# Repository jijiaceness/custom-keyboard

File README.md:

# My Custom Keyboard: Overview

This is a fully custom 55-key split mechanical keyboard built from scratch, from the PCB to the 3D-printed case, developed with the support of Hack Club Program Keeb. 
I came into this project with almost no knowledge of how a keyboard works or the parts it consisted of, and over this two-month journey, I learned how to make all the components that make up a functional keyboard.

## Features
- Unique split keyboard layout
- Ergonomic ortholinear and column-staggered keys
- RJ45 socket connecting the two sides that supports hot-plugging
- 3D-printed top mount case with a base, plate, and top frame
- QMK firmware support with 3 custom layers

## Why I Built It

I've been wanting a split keyboard for a while after typing for hours on my laptop and experiencing hand pain and cramps. Mechanical keyboards have always appealed to me, and the Hack Club program Keeb was a great opportunity for me to build my own while learning the inner workings of a keyboard. I also liked the idea of how customizable my own keyboard would be as I could code what each key does instead of relying on the built-in funcitonality.

## What I Learned

Again, I came into this endeavor with no idea what a switch even was, so I most likely learned more from building this keyboard than in any of my year-long classes at school. 

I learned ...
- What a PCB actually does and its relation to a microcontroller
- How to make a PCB from scratch
- How to use Onshape and how to 3D-design with parametric modeling
- The different parts of a keyboard (switches, diodes, stabilizers, sockets, microcontroller, etc.)
- The software that makes your computer actually recognize and process keyboard input
- How to write the software and tailor it to my design
    - The relation between keymaps.c, keyboard.h, and info.json was particularly interesting; I didn't know that the matrix in info.json was based on the physical positioning of the switches

## Challenges

The biggest challenge was definitely getting used to the applications (KiCad and Onshape) and their workflow. Not understanding the right sequence and way to do things, even with the help of Keeb's guide, cost me many hours of redoing things and searching into the depths of the internet to fix.

  For KiCad, I didn't really finalize my layout on the schematic before moving onto the PCB editor and also put my left and right PCB on the same project, which went against KiCad's method of designing PCBs. I spent a lot of time moving the right PCB into a new project but still had to redo most of it.

  For Onshape, I had no idea how to properly constrain my sketches, and my first iterations were filled with haphazard lengths and angles. I probably redid my sketch 10 times while designing the case. I do feel proud now in how far I've come in CADing since the beginning, and my sketches are much cleaner now.

# Keyboard Overview

## Schematic
### Left schematic

### Right schematic

## PCB

### 3D view
|left view|right view|
| --- | --- |
|  |  |

## Case
### Left Case

<br>

### Right Case

<br>

# Bill of Materials (BOM)

|Item|Name                        |Quantity|Notes                                             |Cost (USD)|
|----|----------------------------|--------|--------------------------------------------------|----------|
|1   |Raspberry Pi Pico           |2       |SC0916                                            |$7.82     |
|2   |Left PCB from JLCPCB        |1       |                                                  |$13.8     |
|3   |Right PCB from JLCPCB       |1       |                                                  |$13.8     |
|4   |Cherry MX Switches          |55      |70 count, Orange key switch.                      |$16.8     |
|5   |1N4148 Diodes               |55      |100 count                                         |$3.91     |
|6   |M3xD4.6xL3.0 heatset inserts|52      |100 count                                         |$5.18     |
|7   |M3x5mm screws               |7       |50 count                                          |$2.56     |
|8   |M3x14mm screws              |6       |50 count                                          |$3.54     |
|9   |RJ45 Shield Network Jack    |2       |Comes in pack of 2, RJHSE-XM80                    |$3.82     |
|10  |Micro USB to USB-A Cable    |1       |1m                                                |$2.6      |
|11  |USB-A to USB-C adapter      |1       |                                                  |$3.45     |
|12  |Rj45 Connector              |1       |0.5m                                              |$4.37     |
|13  |DSA Blank Custom Keycaps    |62      |85 pcs (any keycaps bigger than 1u counts as 2 pcs|$32.94    |
|14  |                            |        |                                                  |          |
|    |TOTAL                       |        |                                                  |$114.59   |

# Credits

This project was possible due to the numerous open-source projects and resources, especially the [the keyther by MagoSaronno](https://github.com/MagoSaronno/keyther/tree/main) as well as many other detailed in the journal. Finally, thank you to Hack Club Keeb for providing the guides and opportunity for me to build a keyboard!

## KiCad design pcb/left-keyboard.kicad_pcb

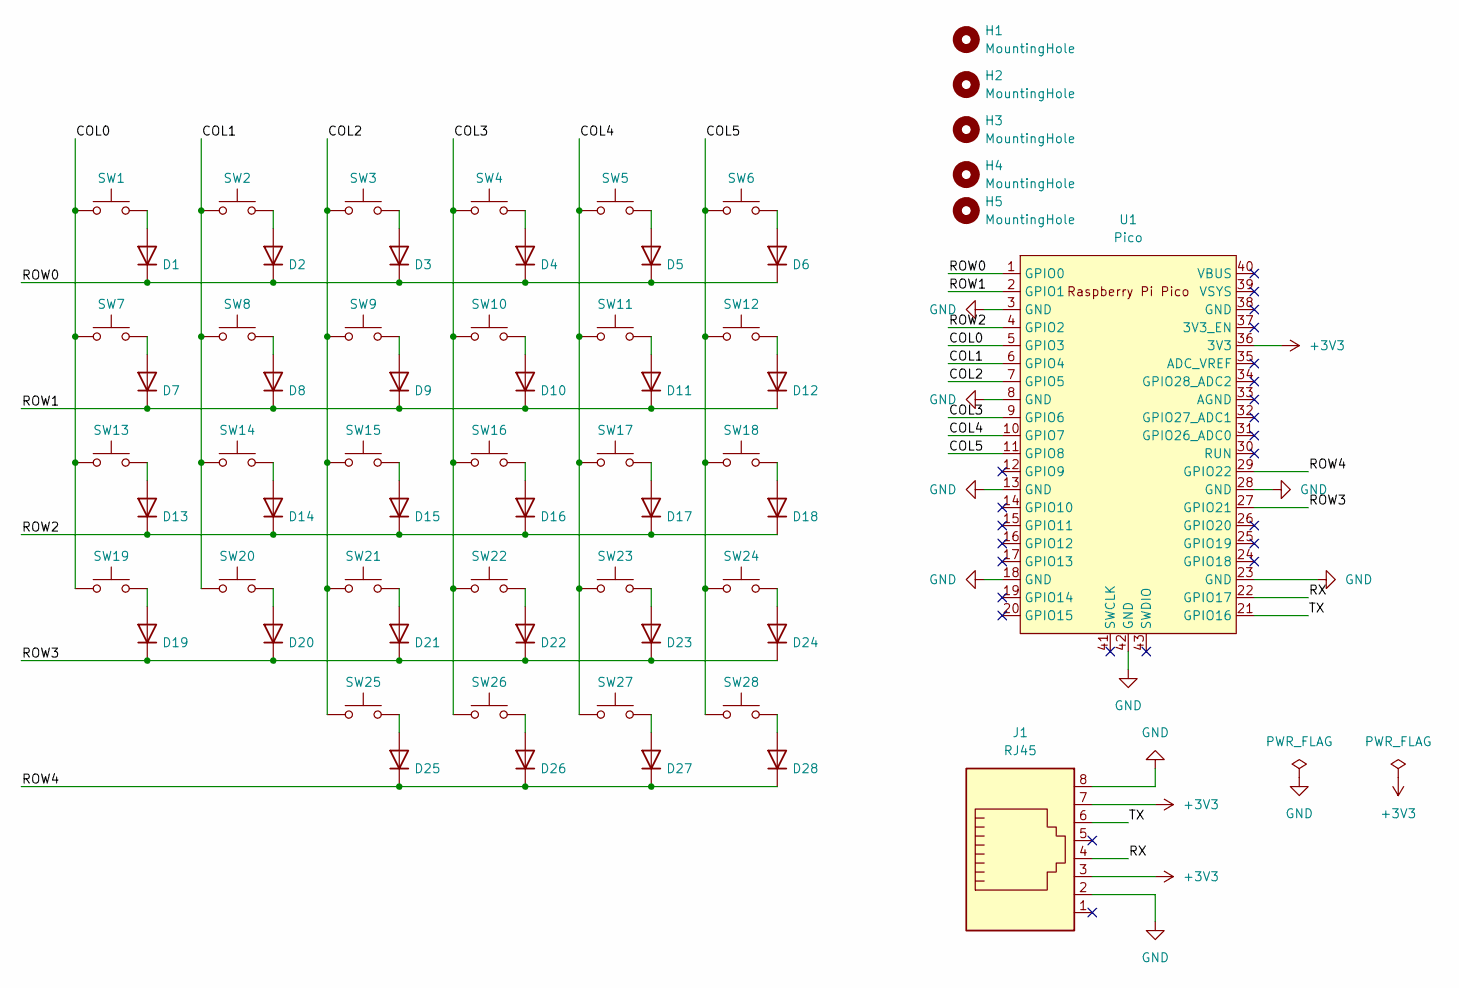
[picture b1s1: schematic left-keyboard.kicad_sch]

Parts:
D1, D2, D3, D4, D5, D6, D7, D8, D9, D10, D11, D12, D13, D14, D15, D16, D17, D18, D19, D20, D21, D22, D23, D24, D25, D26, D27, D28: 1N4148; D_DO-35_SOD27_P7.62mm_Horizontal
H1, H2, H3, H4, H5: MountingHole; MountingHole_3.2mm_M3
J1: RJ45; RJ45_Amphenol_RJHSE5380
SW1, SW2, SW3, SW4, SW5, SW6, SW8, SW9, SW10, SW11, SW12, SW14, SW15, SW16, SW17, SW18, SW20, SW21, SW22, SW23, SW24, SW25, SW26, SW27, SW28: SW_Push; SW_MX_1u
SW7: SW_Push; SW_MX_1.25u
SW13: SW_Push; SW_MX_1.5u
SW19: SW_Push; SW_MX_1.75u
U1: Pico; RPi_Pico_SMD_TH

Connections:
+3V3: J1.3, J1.7, U1.36 (3V3)
/COL0: SW1.1, SW7.1, SW13.1, SW19.1, U1.5 (GPIO3)
/COL1: SW2.1, SW8.1, SW14.1, SW20.1, U1.6 (GPIO4)
/COL2: SW3.1, SW9.1, SW15.1, SW21.1, SW25.1, U1.7 (GPIO5)
/COL3: SW4.1, SW10.1, SW16.1, SW22.1, SW26.1, U1.9 (GPIO6)
/COL4: SW5.1, SW11.1, SW17.1, SW23.1, SW27.1, U1.10 (GPIO7)
/COL5: SW6.1, SW12.1, SW18.1, SW24.1, SW28.1, U1.11 (GPIO8)
/ROW0: D1.1 (K), D2.1 (K), D3.1 (K), D4.1 (K), D5.1 (K), D6.1 (K), U1.1 (GPIO0)
/ROW1: D7.1 (K), D8.1 (K), D9.1 (K), D10.1 (K), D11.1 (K), D12.1 (K), U1.2 (GPIO1)
/ROW2: D13.1 (K), D14.1 (K), D15.1 (K), D16.1 (K), D17.1 (K), D18.1 (K), U1.4 (GPIO2)
/ROW3: D19.1 (K), D20.1 (K), D21.1 (K), D22.1 (K), D23.1 (K), D24.1 (K), U1.27 (GPIO21)
/ROW4: D25.1 (K), D26.1 (K), D27.1 (K), D28.1 (K), U1.29 (GPIO22)
/RX: J1.4, U1.22 (GPIO17)
/TX: J1.6, U1.21 (GPIO16)
GND: J1.2, J1.8, U1.3 (GND), U1.8 (GND), U1.13 (GND), U1.18 (GND), U1.23 (GND), U1.28 (GND), U1.42 (GND)
unnamed: D1.2 (A), SW1.2
unnamed: D2.2 (A), SW2.2
unnamed: D3.2 (A), SW3.2
unnamed: D4.2 (A), SW4.2
unnamed: D5.2 (A), SW5.2
unnamed: D6.2 (A), SW6.2
unnamed: D7.2 (A), SW7.2
unnamed: D8.2 (A), SW8.2
unnamed: D9.2 (A), SW9.2
unnamed: D10.2 (A), SW10.2
unnamed: D11.2 (A), SW11.2
unnamed: D12.2 (A), SW12.2
unnamed: D13.2 (A), SW13.2
unnamed: D14.2 (A), SW14.2
unnamed: D15.2 (A), SW15.2
unnamed: D16.2 (A), SW16.2
unnamed: D17.2 (A), SW17.2
unnamed: D18.2 (A), SW18.2
unnamed: D19.2 (A), SW19.2
unnamed: D20.2 (A), SW20.2
unnamed: D21.2 (A), SW21.2
unnamed: D22.2 (A), SW22.2
unnamed: D23.2 (A), SW23.2
unnamed: D24.2 (A), SW24.2
unnamed: D25.2 (A), SW25.2
unnamed: D26.2 (A), SW26.2
unnamed: D27.2 (A), SW27.2
unnamed: D28.2 (A), SW28.2

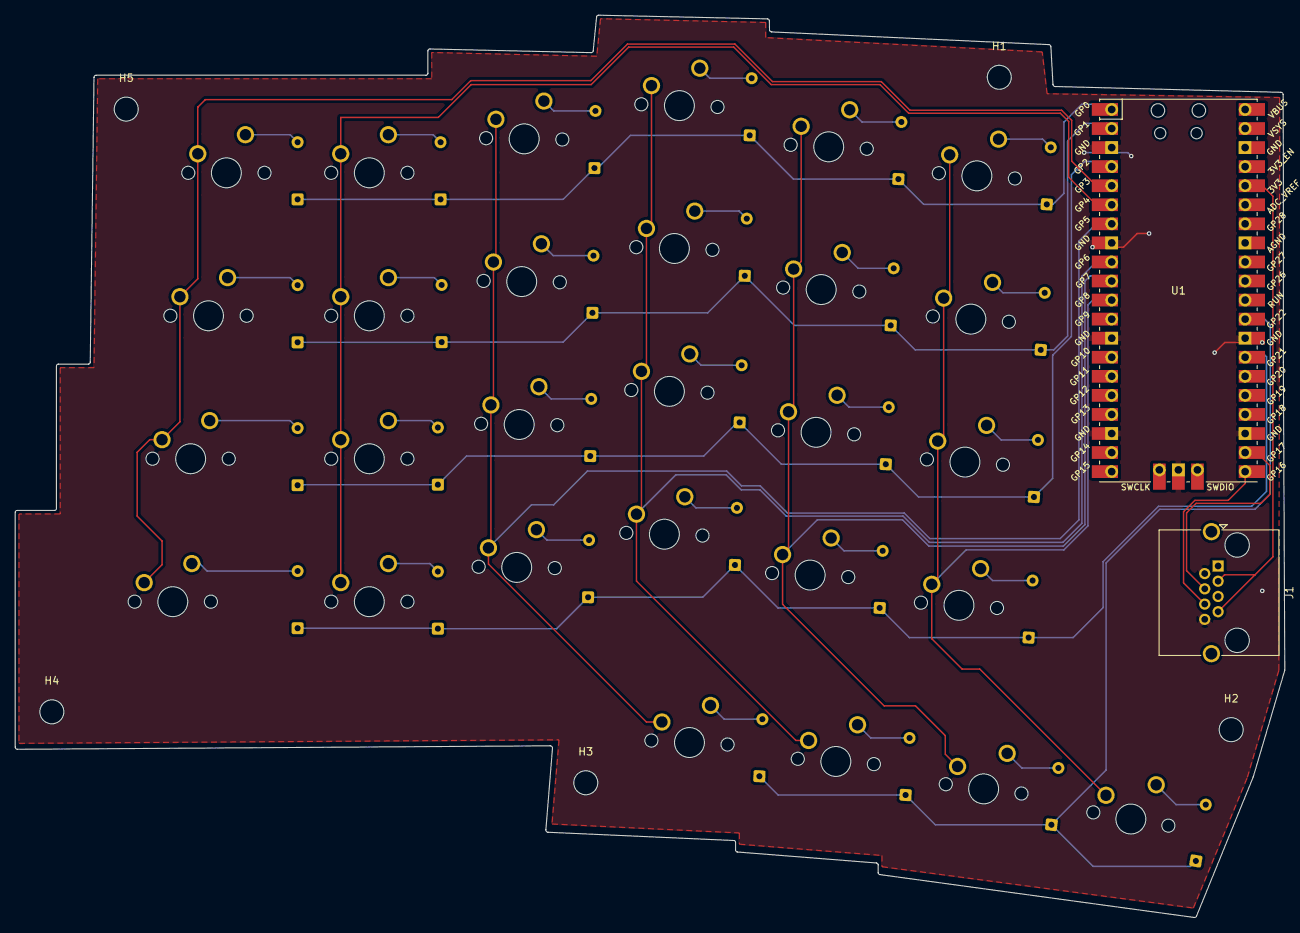
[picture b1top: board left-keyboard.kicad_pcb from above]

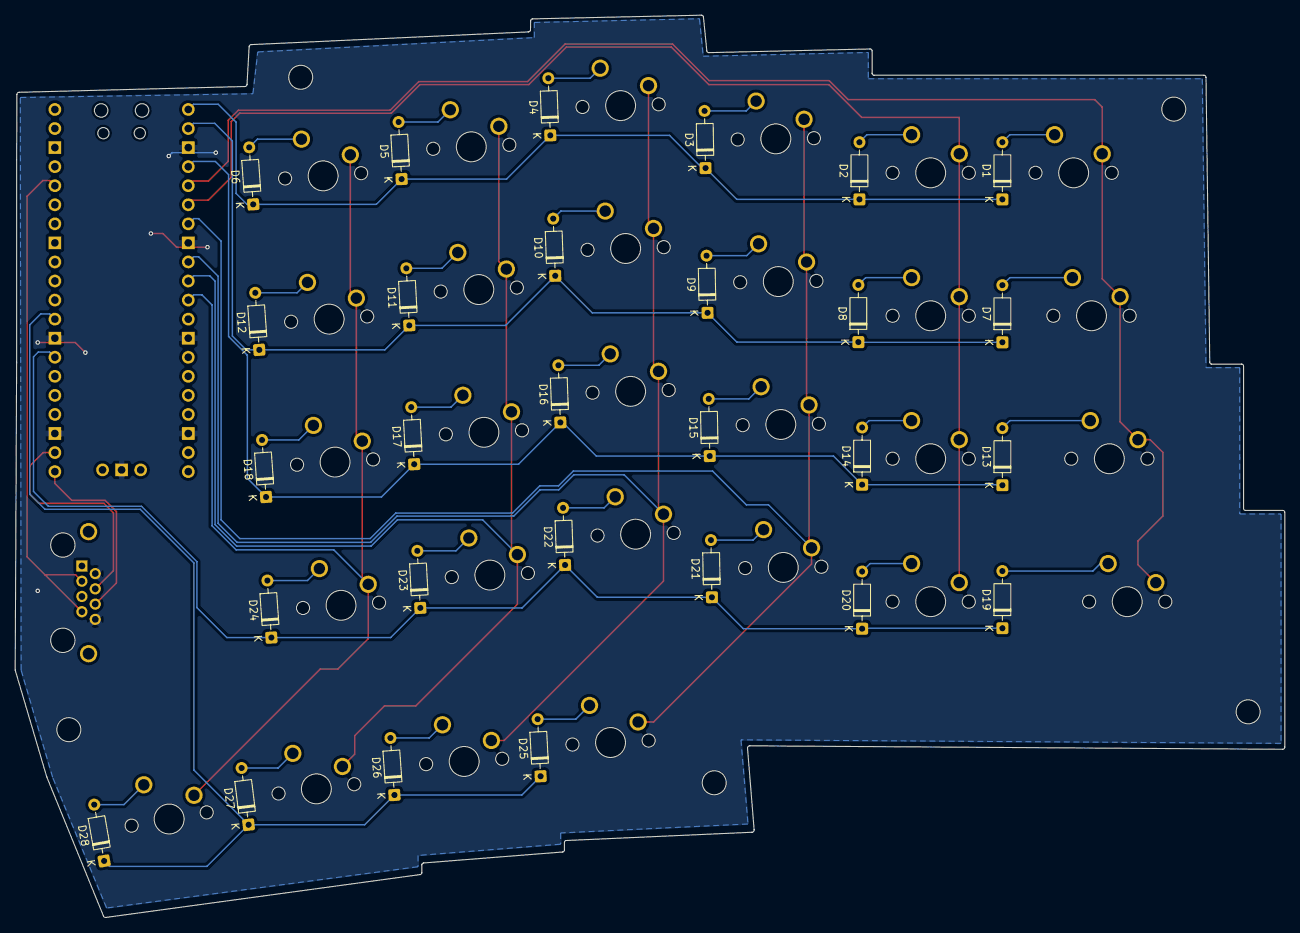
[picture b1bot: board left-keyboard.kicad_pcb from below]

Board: 2 copper layers, 169.2 x 120.2 mm, 63 parts (28 on the bottom side), 43 nets.
